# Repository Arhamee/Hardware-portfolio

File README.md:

<div align="center">

# ⚡ Hardware Portfolio
### Arham Amir

**Electronics Engineering @ NED University, Karachi** · Class of 2028

Multi-layer PCB designs — schematic capture to fabrication-ready output.  
Every board includes the full KiCad source, renders, and DRC verification.

</div>

---

## 📂 Projects

| # | Project | Layers | Key Focus | Status |
|:---:|---|:---:|---|:---:|
| 01 | **[LattePanda Mu Carrier Board](./01-LattePanda-Mu-Carrier-Board)** | 4 | USB 3.0 · HDMI · GbE, controlled impedance | 🟡 In Progress |
| 02 | **[BGA Smart USB Drive](./02-BGA-Smart-USB-Drive)** | 4 | RP2040 + 64GB eMMC, 0.5mm BGA escape | 🟢 Complete |
| 03 | **[Industrial APFC System](./03-Industrial-APFC-System)** | 4 | 5kW single-phase, mains isolation | 🟢 Complete |
| 04 | **[STM32WB USB + RF Board](./04-STM32WB-USB-RF)** | 4 | 2.4GHz RF + USB, dual-ground stackup | 🟢 Complete |
| 05 | **[USB-C PD Power Supply](./05-USBC-PD-Power-Supply)** | 2 | CH224K PD negotiation, 90Ω diff pairs | 🟢 Complete |
| 06 | **[ESP32 Power Monitor](./06-ESP32-Power-Monitor)** | 4 | 5-channel relay + current sensing | 🟢 Complete |
| 07 | **[Hearing Assist DSP](./07-Hearing-Assist-DSP)** | — | Real-time NLMS noise cancellation | ✅ Built & Tested |
| 09 | **[MCU Board Collection](./09-MCU-Board-Collection)** | 2–4 | ESP32 / STM32 / MSPM0 variants | 🟢 Mixed |

---

## 🛠️ Technical Focus

<table>
<tr>
<td valign="top" width="50%">

**PCB Design**
- Controlled-impedance routing
- Differential pair matching
- Fine-pitch BGA fanout (via-in-pad, dogbone)
- Multi-layer stackup planning
- PDN design across multiple rails
- DFM / DRC verification

</td>
<td valign="top" width="50%">

**Embedded & Digital**
- ESP32 · STM32 · RP2040 · TI MSPM0
- FreeRTOS · real-time DSP
- Verilog RTL · FSM design
- ModelSim simulation

</td>
</tr>
<tr>
<td valign="top" colspan="2">

**Power Electronics**
- Mains-side isolation
- Protection: MOV, TVS, fusing
- SSR switching · boost/LDO regulation

</td>
</tr>
</table>
---
## 📁 Repository Structure

Each project folder follows the same layout:

```
project-name/
├── README.md              — design overview, challenges, decisions
├── kicad-project/          — full KiCad source (.kicad_pro/.sch/.pcb)
├── schematic.pdf           — exported schematic view
├── pcb-layout-top.png      — routed board, top view
├── 3d-render-top.png       — 3D render
├── drc-report.png          — DRC/ERC verification result
└── gerbers.zip             — fabrication-ready Gerbers + drill files
```

> Every board ships with its **raw KiCad files** — not just images — so the
> design can be opened, checked, and verified directly rather than taken on faith.
### 🔍 Fabrication Status

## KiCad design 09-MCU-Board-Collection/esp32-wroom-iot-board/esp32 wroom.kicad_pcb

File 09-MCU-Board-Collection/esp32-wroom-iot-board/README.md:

# General-Purpose IoT Board — ESP32-WROOM

4-layer board built around the ESP32-WROOM module as a versatile, expandable
IoT development platform.

## Features
- **Si7021** — I²C temperature and humidity sensor
- **QWIIC connector** — plug-and-play expansion for other I²C devices
- **CP2104** — USB-to-serial UART with onboard programmer, no external
  programmer needed
- **RGB LED + button** — status indication and user input
- **Screw terminals** — LED strip interface, 4-level converted outputs,
  fused power supply
- **Power relay** — control for high-power devices (lights, motors, appliances)

## Why 4 layers
Cleaner routing and better signal integrity for the ESP32's high-speed
requirements, especially with multiple peripherals sharing the board.

## Tool
KiCad 9

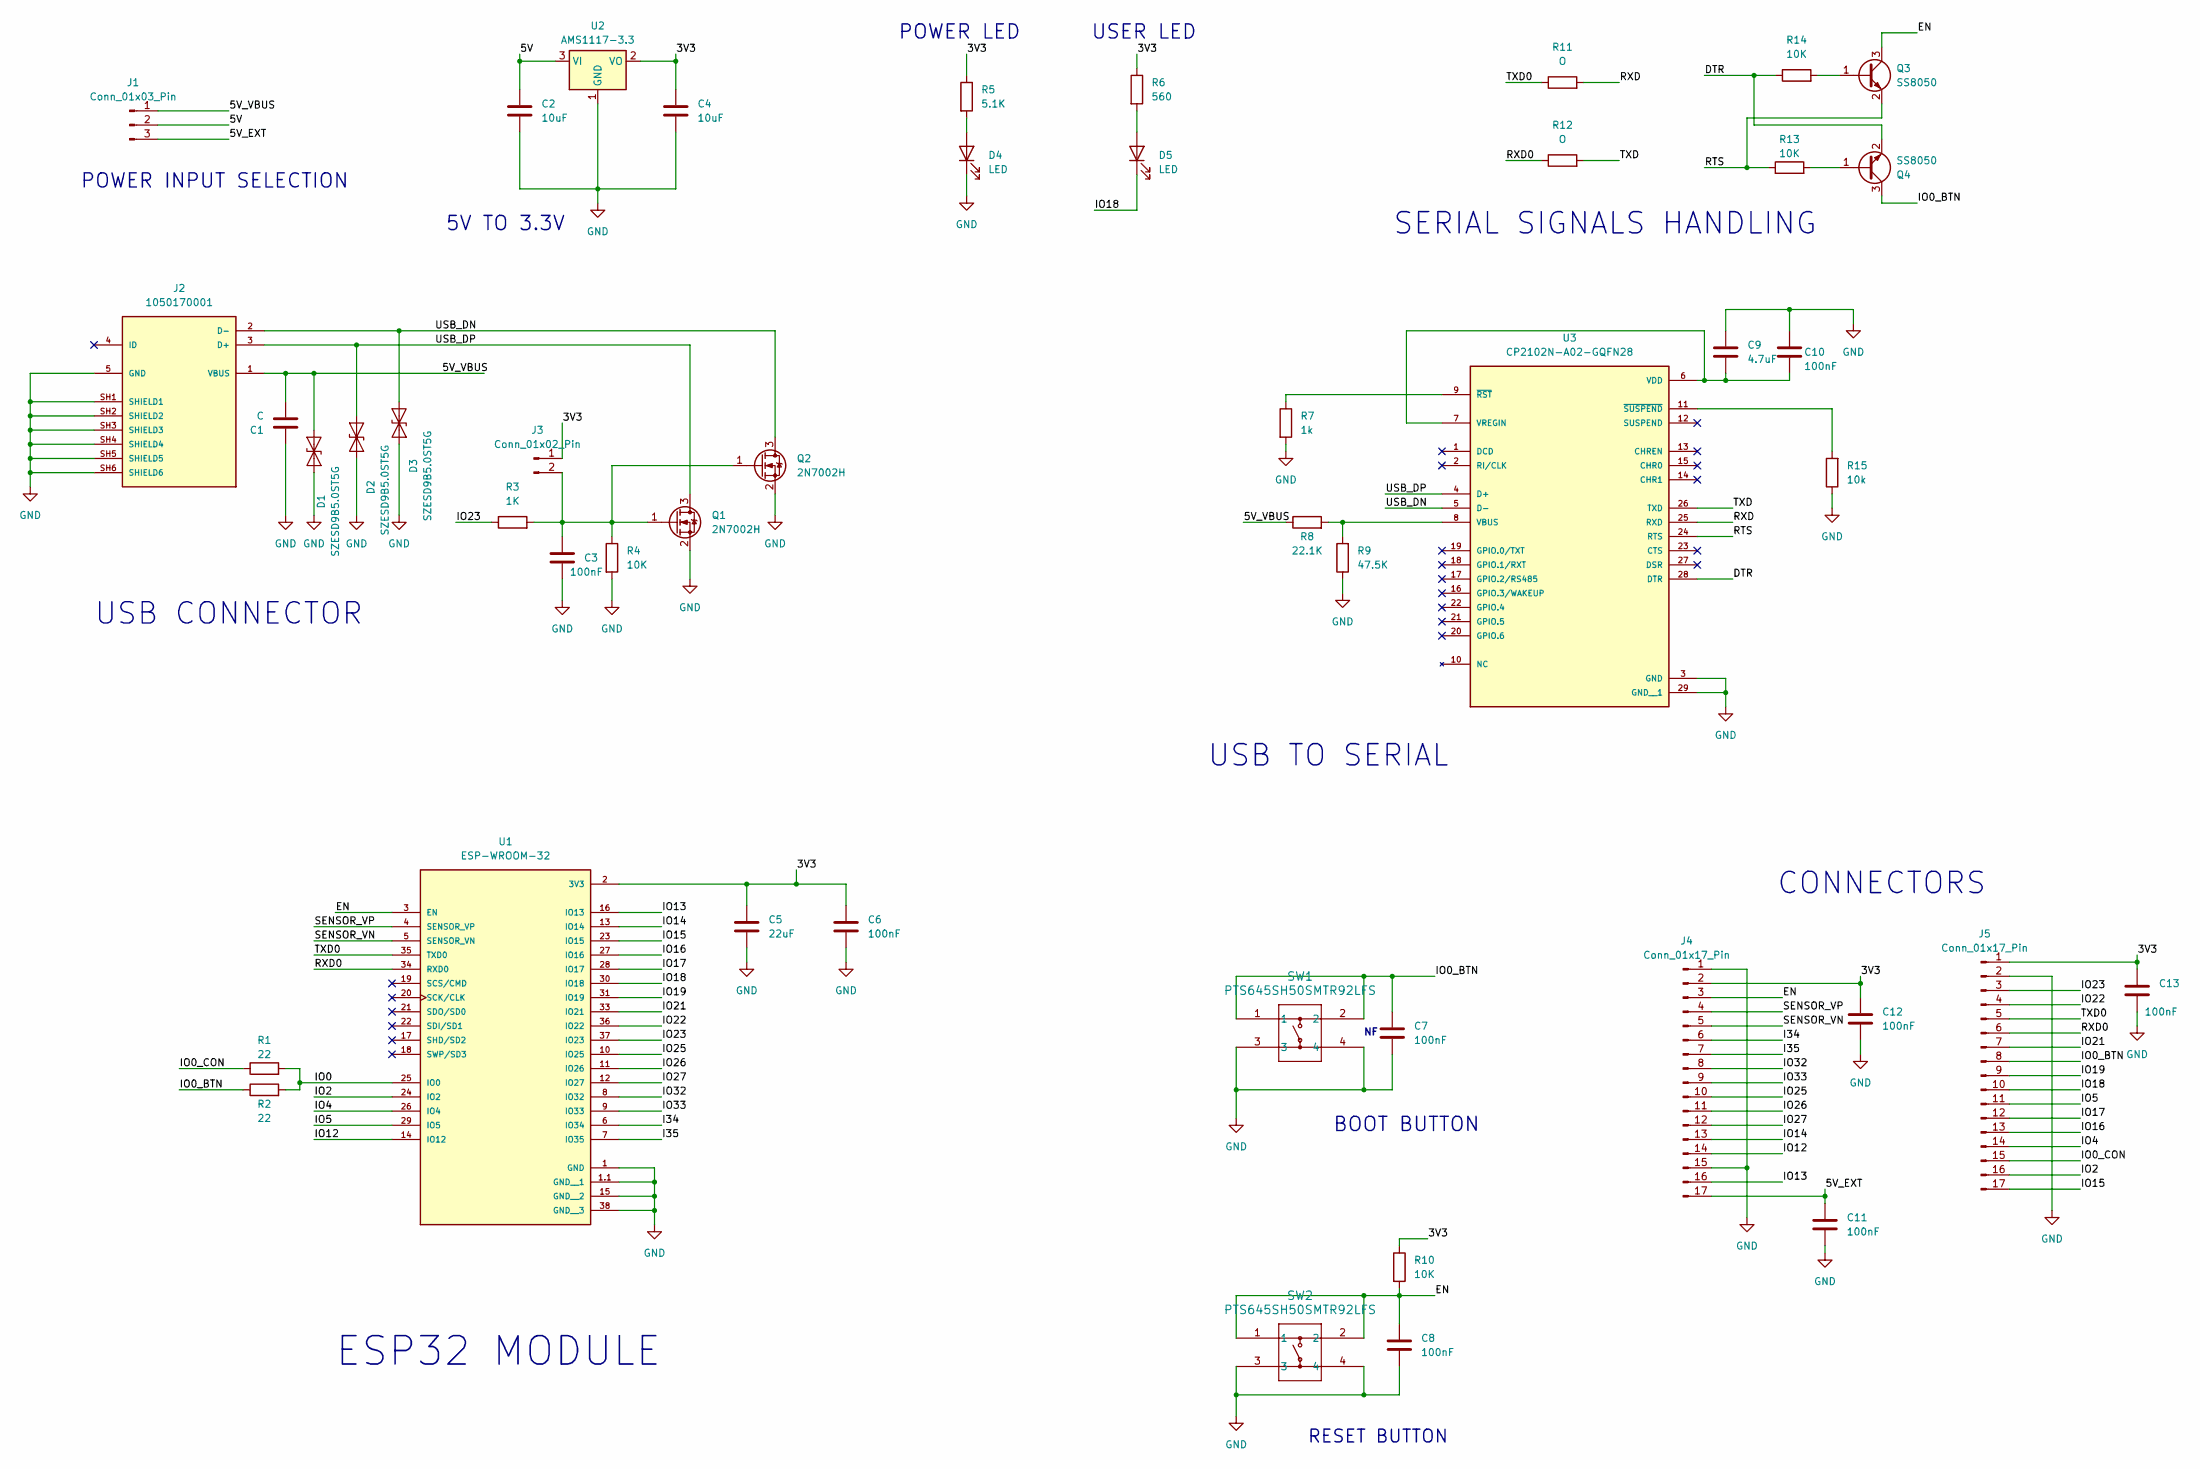
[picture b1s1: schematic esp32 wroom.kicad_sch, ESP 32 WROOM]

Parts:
C1: C; C_0402_1005Metric_Pad0.74x0.62mm_HandSolder
C2, C4: 10uF; C_0402_1005Metric_Pad0.74x0.62mm_HandSolder
C3, C6, C7, C8, C10, C11, C12, C13: 100nF; C_0402_1005Metric_Pad0.74x0.62mm_HandSolder
C5: 22uF; C_0402_1005Metric_Pad0.74x0.62mm_HandSolder
C9: 4.7uF; C_0402_1005Metric_Pad0.74x0.62mm_HandSolder
D1, D2, D3: SZESD9B5.0ST5G; D_SOD-923
D4, D5: LED; LED_0402_1005Metric_Pad0.77x0.64mm_HandSolder
J1: Conn_01x03_Pin; PinHeader_1x03_P1.27mm_Vertical
J2: 1050170001; MOLEX_1050170001; PARTREV F
J3: Conn_01x02_Pin; PinHeader_1x02_P1.27mm_Vertical
J4, J5: Conn_01x17_Pin; PinHeader_1x17_P1.27mm_Vertical
Q1, Q2: 2N7002H; SOT-23
Q3, Q4: SS8050; SOT-23
R1, R2: 22; R_0402_1005Metric_Pad0.72x0.64mm_HandSolder
R3: 1K; R_0402_1005Metric_Pad0.72x0.64mm_HandSolder
R4, R10, R13, R14: 10K; R_0402_1005Metric_Pad0.72x0.64mm_HandSolder
R5: 5.1K; R_0402_1005Metric_Pad0.72x0.64mm_HandSolder
R6: 560; R_0402_1005Metric_Pad0.72x0.64mm_HandSolder
R7: 1k; R_0402_1005Metric_Pad0.72x0.64mm_HandSolder
R8: 22.1K; R_0402_1005Metric_Pad0.72x0.64mm_HandSolder
R9: 47.5K; R_0402_1005Metric_Pad0.72x0.64mm_HandSolder
R11, R12: O; R_0402_1005Metric_Pad0.72x0.64mm_HandSolder
R15: 10k; R_0402_1005Metric_Pad0.72x0.64mm_HandSolder
SW1, SW2: PTS645SH50SMTR92LFS; PTS645S_SMTR92_CNK
U1: ESP-WROOM-32; MODULE_ESP-WROOM-32
U2: AMS1117-3.3; SOT-223-3_TabPin2
U3: CP2102N-A02-GQFN28; QFN50P500X500X80-29N; PARTREV 1.5

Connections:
/3V3: C4.1, C5.1, C6.1, C12.1, C13.1, J3.1, J4.2, J5.1, R5.1, R6.1, R10.1, U1.2 (3V3), U2.2 (VO)
/5V: C2.1, J1.2, U2.3 (VI)
/5V_EXT: C11.1, J1.3, J4.17
/5V_VBUS: C1.2, D1.2 (A2), J1.1, J2.1 (VBUS), R8.1
/DTR: Q4.2 (E), R14.1, U3.28 (DTR)
/EN: C8.1, J4.3, Q3.3 (C), R10.2, SW2.1, SW2.2, U1.3 (EN)
/I34: J4.6, U1.6 (IO34)
/I35: J4.7, U1.7 (IO35)
/IO0: R1.2, R2.2, U1.25 (IO0)
/IO0_BTN: C7.1, J5.8, Q4.3 (C), R2.1, SW1.1, SW1.2
/IO0_CON: J5.15, R1.1
/IO2: J5.16, U1.24 (IO2)
/IO4: J5.14, U1.26 (IO4)
/IO5: J5.11, U1.29 (IO5)
/IO12: J4.14, U1.14 (IO12)
/IO13: J4.16, U1.16 (IO13)
/IO14: J4.13, U1.13 (IO14)
/IO15: J5.17, U1.23 (IO15)
/IO16: J5.13, U1.27 (IO16)
/IO17: J5.12, U1.28 (IO17)
/IO18: D5.1 (K), J5.10, U1.30 (IO18)
/IO19: J5.9, U1.31 (IO19)
/IO21: J5.7, U1.33 (IO21)
/IO22: J5.4, U1.36 (IO22)
/IO23: J5.3, R3.1, U1.37 (IO23)
/IO25: J4.10, U1.10 (IO25)
/IO26: J4.11, U1.11 (IO26)
/IO27: J4.12, U1.12 (IO27)
/IO32: J4.8, U1.8 (IO32)
/IO33: J4.9, U1.9 (IO33)
/RTS: Q3.2 (E), R13.1, U3.24 (RTS)
/RXD: R11.2, U3.25 (RXD)
/RXD0: J5.6, R12.1, U1.34 (RXD0)
/SENSOR_VN: J4.5, U1.5 (SENSOR_VN)
/SENSOR_VP: J4.4, U1.4 (SENSOR_VP)
/TXD: R12.2, U3.26 (TXD)
/TXD0: J5.5, R11.1, U1.35 (TXD0)
/USB_DN: D3.2 (A2), J2.2 (D-), Q2.3 (D), U3.5 (D-)
/USB_DP: D2.2 (A2), J2.3 (D+), Q1.3 (D), U3.4 (D+)
GND: C1.1, C2.2, C3.2, C4.2, C5.2, C6.2, C7.2, C8.2, C9.1, C10.1, C11.2, C12.2, C13.2, D1.1 (A1), D2.1 (A1), D3.1 (A1), D4.1 (K), J2.5 (GND), J2.SH1 (SHIELD1), J2.SH2 (SHIELD2), J2.SH3 (SHIELD3), J2.SH4 (SHIELD4), J2.SH5 (SHIELD5), J2.SH6 (SHIELD6), J4.1, J4.15, J5.2, Q1.2 (S), Q2.2 (S), R4.2, R7.2, R9.1, R15.1, SW1.3, SW1.4, SW2.3, SW2.4, U1.1 (GND), U1.1.1 (GND__1), U1.15 (GND__2), U1.38 (GND__3), U2.1 (GND), U3.3 (GND), U3.29 (GND__1)
unnamed: D4.2 (A), R5.2
unnamed: D5.2 (A), R6.2
unnamed: C3.1, J3.2, Q1.1 (G), Q2.1 (G), R3.2, R4.1
unnamed: Q3.1 (B), R14.2
unnamed: Q4.1 (B), R13.2
unnamed: R8.2, R9.2, U3.8 (VBUS)
unnamed: C9.2, C10.2, U3.6 (VDD), U3.7 (VREGIN)
unnamed: R7.1, U3.9 (~RST)
unnamed: R15.2, U3.11 (~SUSPEND)

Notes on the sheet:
USB TO SERIAL
SERIAL SIGNALS HANDLING
ESP32 MODULE
USB CONNECTOR
BOOT BUTTON
USER LED
RESET BUTTON
POWER INPUT SELECTION
POWER LED
CONNECTORS
5V TO 3.3V

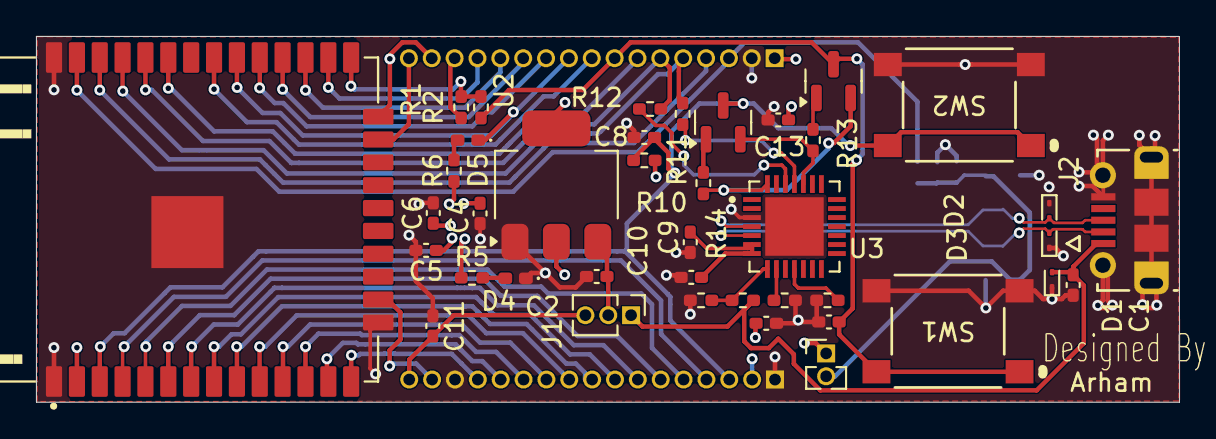
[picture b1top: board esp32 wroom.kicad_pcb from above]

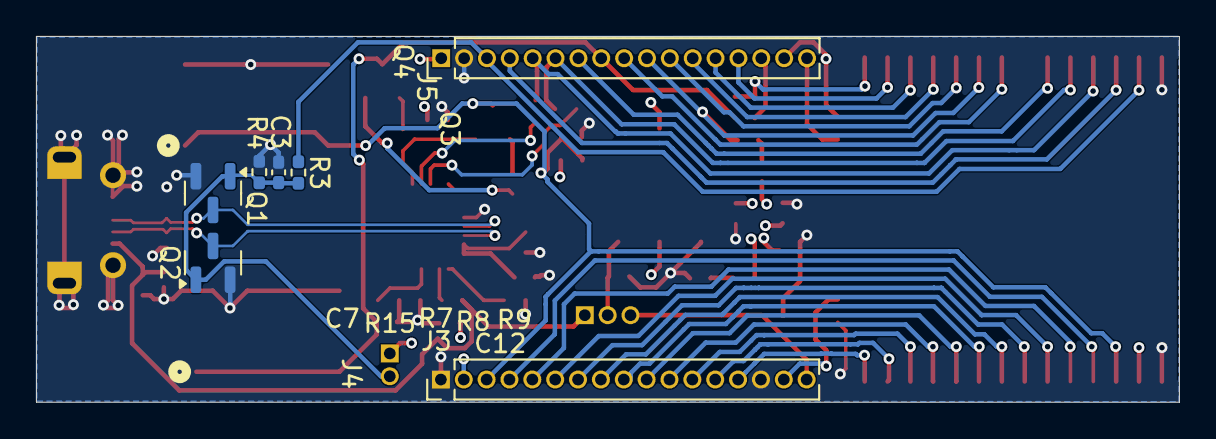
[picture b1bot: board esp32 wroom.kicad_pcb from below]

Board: 4 copper layers, 63.5 x 20.3 mm, 47 parts (7 on the bottom side), 49 nets.

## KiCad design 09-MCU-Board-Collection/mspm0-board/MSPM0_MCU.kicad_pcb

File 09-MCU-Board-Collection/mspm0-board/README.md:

# MSPM0 Board — TI ARM Cortex-M0+

First design using Texas Instruments' MSPM0 family.

## Focus Areas
- Clean power delivery
- Robust USB connectivity
- MCU-to-peripheral signal routing
- Careful attention to datasheet guidance for decoupling, crystal layout,
  and USB differential pairs

## Tool
KiCad 9

## Reference
Built following Phil's Lab's MSPM0 hardware tutorial.

## Status
Design complete — assembly and testing planned.

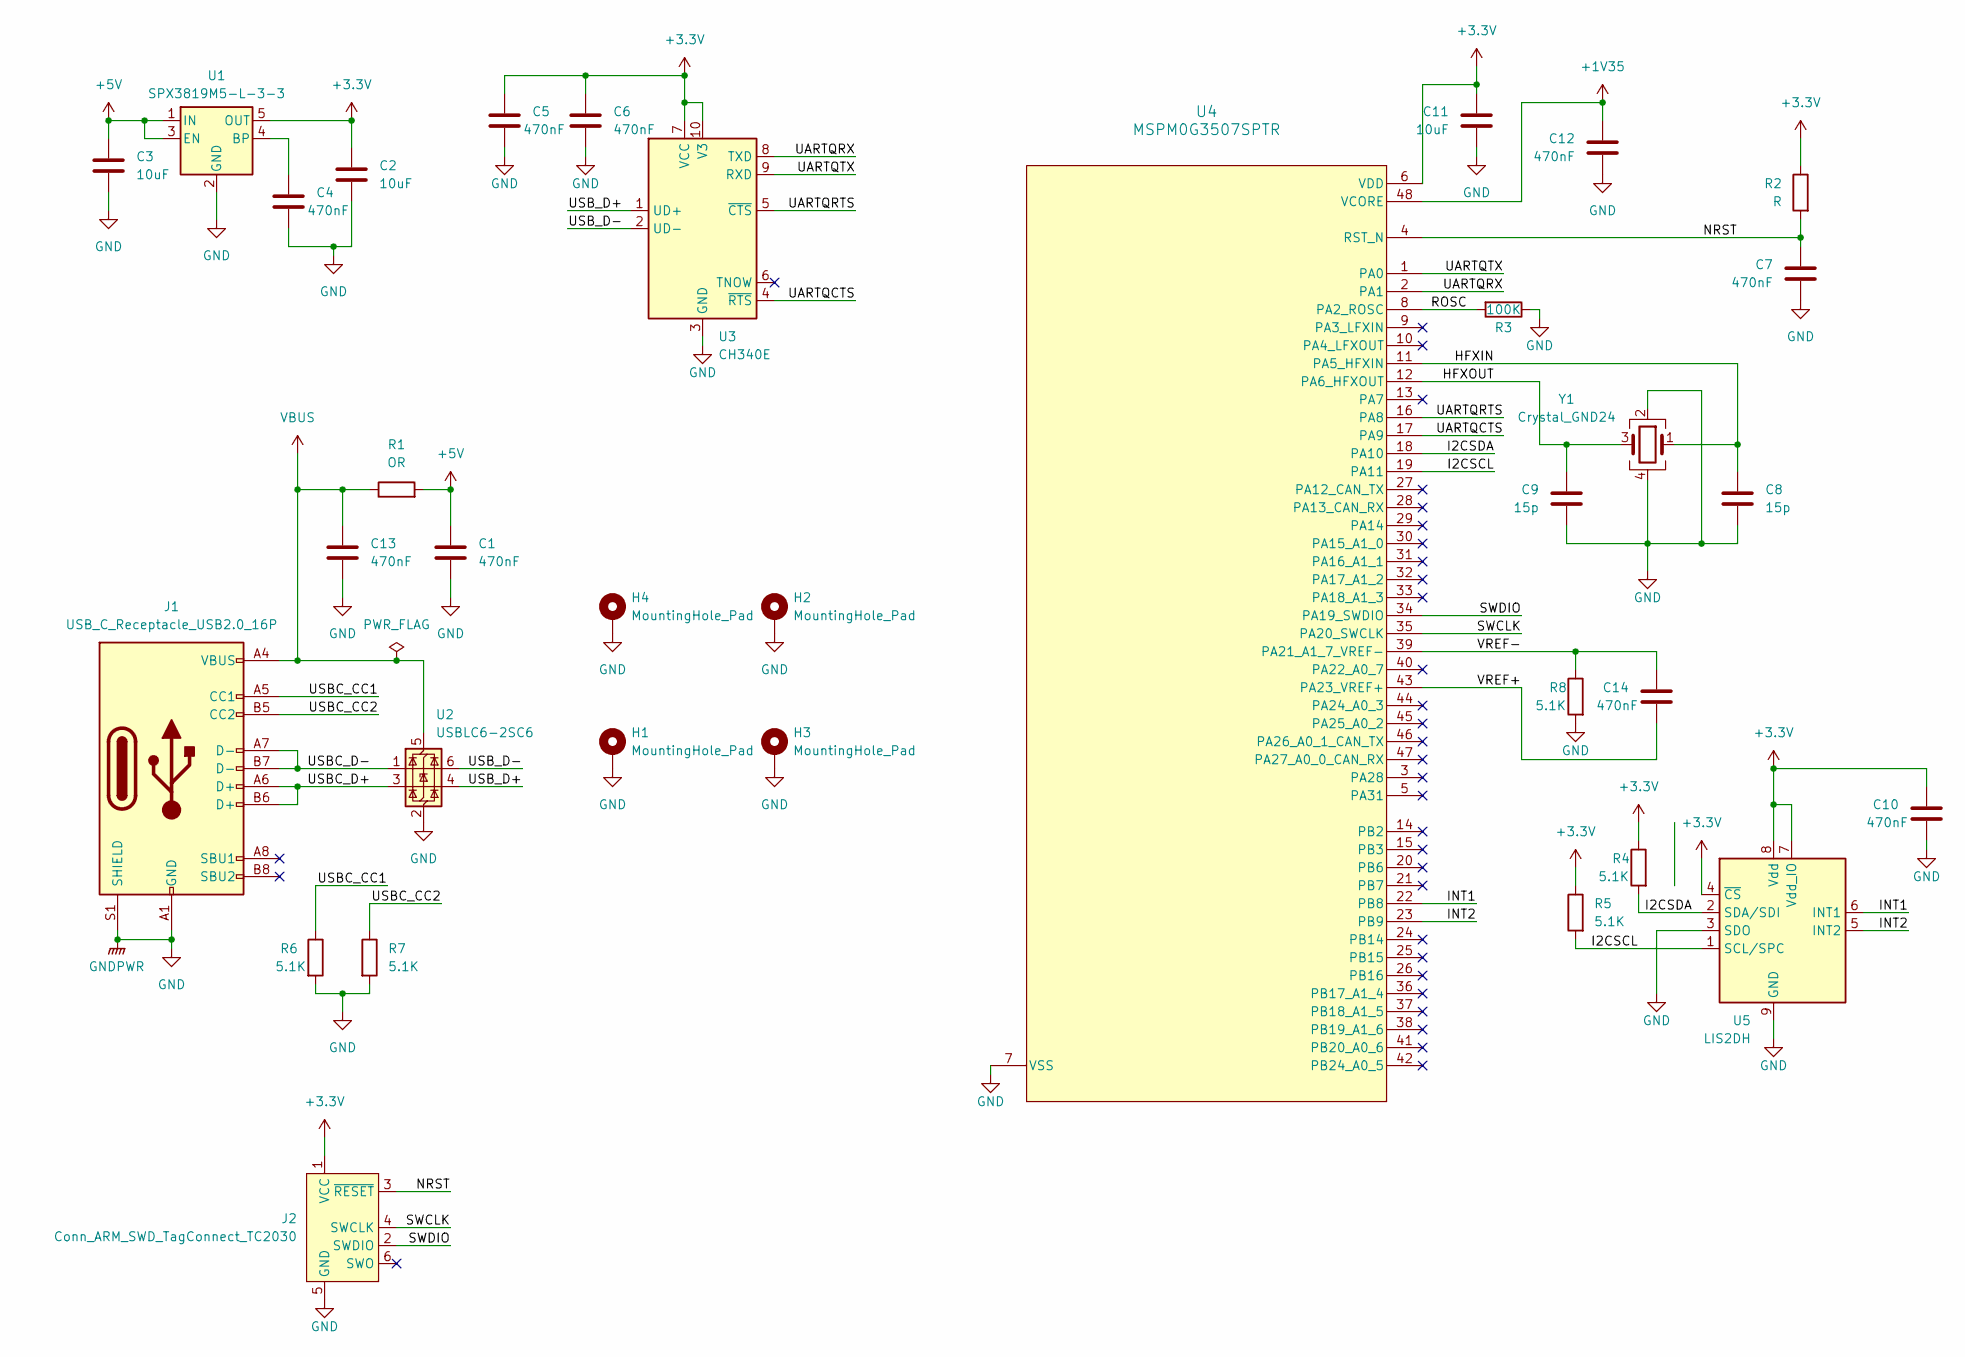
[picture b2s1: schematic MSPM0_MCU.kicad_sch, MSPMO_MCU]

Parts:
C1, C4, C5, C6, C7, C10, C12, C13, C14: 470nF; C_0603_1608Metric_Pad1.08x0.95mm_HandSolder
C2, C3, C11: 10uF; C_0805_2012Metric_Pad1.18x1.45mm_HandSolder
C8, C9: 15p; C_0603_1608Metric_Pad1.08x0.95mm_HandSolder
H1, H2, H3, H4: MountingHole_Pad; MountingHole_3.2mm_M3_Pad_Via
J1: USB_C_Receptacle_USB2.0_16P; USB_C_Receptacle_GCT_USB4105-xx-A_16P_TopMnt_Horizontal
J2: Conn_ARM_SWD_TagConnect_TC2030; Tag-Connect_TC2030-IDC-FP_2x03_P1.27mm_Vertical
R1: OR; R_0603_1608Metric_Pad0.98x0.95mm_HandSolder
R2: R; R_0603_1608Metric_Pad0.98x0.95mm_HandSolder
R3: 100K; R_0603_1608Metric_Pad0.98x0.95mm_HandSolder
R4, R5, R6, R7, R8: 5.1K; R_0603_1608Metric_Pad0.98x0.95mm_HandSolder
U1: SPX3819M5-L-3-3; SOT-23-5
U2: USBLC6-2SC6; SOT-23-6
U3: CH340E; MSOP-10_3x3mm_P0.5mm
U4: MSPM0G3507SPTR; PT0048A-IPC_A
U5: LIS2DH; LGA-14_2x2mm_P0.35mm_LayoutBorder3x4y
Y1: Crystal_GND24; Crystal_SMD_3225-4Pin_3.2x2.5mm_HandSoldering

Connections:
+1V35: C12.1, U4.48 (VCORE)
+3.3V: C2.1, C5.1, C6.1, C10.1, C11.1, J2.1 (VCC), R2.1, R4.1, R5.1, U1.5 (OUT), U3.7 (VCC), U3.10 (V3), U4.6 (VDD), U5.4 (~CS), U5.7 (Vdd_IO), U5.8 (Vdd)
+5V: C1.1, C3.1, R1.2, U1.1 (IN), U1.3 (EN)
/HFXIN: C8.1, U4.11 (PA5_HFXIN), Y1.1
/HFXOUT: C9.1, U4.12 (PA6_HFXOUT), Y1.3
/I2CSCL: R5.2, U4.19 (PA11), U5.1 (SCL/SPC)
/I2CSDA: R4.2, U4.18 (PA10), U5.2 (SDA/SDI)
/INT1: U4.22 (PB8), U5.6 (INT1)
/INT2: U4.23 (PB9), U5.5 (INT2)
/NRST: C7.1, J2.3 (~RESET), R2.2, U4.4 (RST_N)
/ROSC: R3.2, U4.8 (PA2_ROSC)
/SWCLK: J2.4 (SWCLK), U4.35 (PA20_SWCLK)
/SWDIO: J2.2 (SWDIO), U4.34 (PA19_SWDIO)
/UARTQCTS: U3.4 (~RTS), U4.17 (PA9)
/UARTQRTS: U3.5 (~CTS), U4.16 (PA8)
/UARTQRX: U3.8 (TXD), U4.2 (PA1)
/UARTQTX: U3.9 (RXD), U4.1 (PA0)
/USBC_CC1: J1.A5 (CC1), R6.1
/USBC_CC2: J1.B5 (CC2), R7.1
/USBC_D+: J1.A6 (D+), J1.B6 (D+), U2.3 (I/O2)
/USBC_D-: J1.A7 (D-), J1.B7 (D-), U2.1 (I/O1)
/USB_D+: U2.4 (I/O2), U3.1 (UD+)
/USB_D-: U2.6 (I/O1), U3.2 (UD-)
/VREF+: C14.2, U4.43 (PA23_VREF+)
/VREF-: C14.1, R8.1, U4.39 (PA21_A1_7_VREF-)
GND: C1.2, C2.2, C3.2, C4.2, C5.2, C6.2, C7.2, C8.2, C9.2, C10.2, C11.2, C12.2, C13.2, H1.1, H2.1, H3.1, H4.1, J1.A1 (GND), J1.A12 (GND), J1.B1 (GND), J1.B12 (GND), J1.S1 (SHIELD), J2.5 (GND), R3.1, R6.2, R7.2, R8.2, U1.2 (GND), U2.2 (GND), U3.3 (GND), U4.7 (VSS), U5.3 (SDO), U5.9 (GND), U5.10 (GND), U5.11 (GND), U5.12 (GND), U5.13 (GND), U5.14 (GND), Y1.2, Y1.4
unnamed: C4.1, U1.4 (BP)
VBUS: C13.1, J1.A4 (VBUS), J1.A9 (VBUS), J1.B4 (VBUS), J1.B9 (VBUS), R1.1, U2.5 (VBUS)

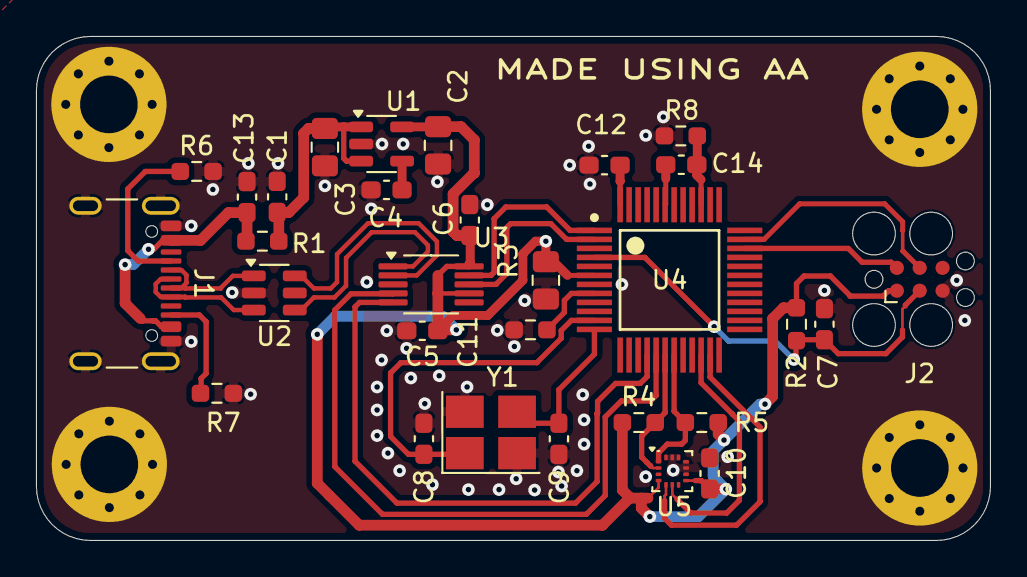
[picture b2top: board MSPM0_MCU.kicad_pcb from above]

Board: 2 copper layers, 53.0 x 28.0 mm, 34 parts (0 on the bottom side), 28 nets.

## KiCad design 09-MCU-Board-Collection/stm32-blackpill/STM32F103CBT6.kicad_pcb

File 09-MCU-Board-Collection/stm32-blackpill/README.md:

# STM32 "Black Pill" Board

First full PCB design completed end-to-end in KiCad 9 — schematic through
2-layer layout and routing.

## Included
- Power management (3.3V LDO)
- Reset circuitry and BOOT configuration
- USB Type-B Micro with proper D+/D− routing
- Careful component placement for signal integrity on a 2-layer board
- DRC passed — ready for prototype manufacturing

## What This Taught Me
MCU power requirements, decoupling strategy, and high-speed signal
considerations — even on a "simple" 2-layer board.

## Reference
Built following Phil Salmony's (Phil's Lab) PCB Design Course.

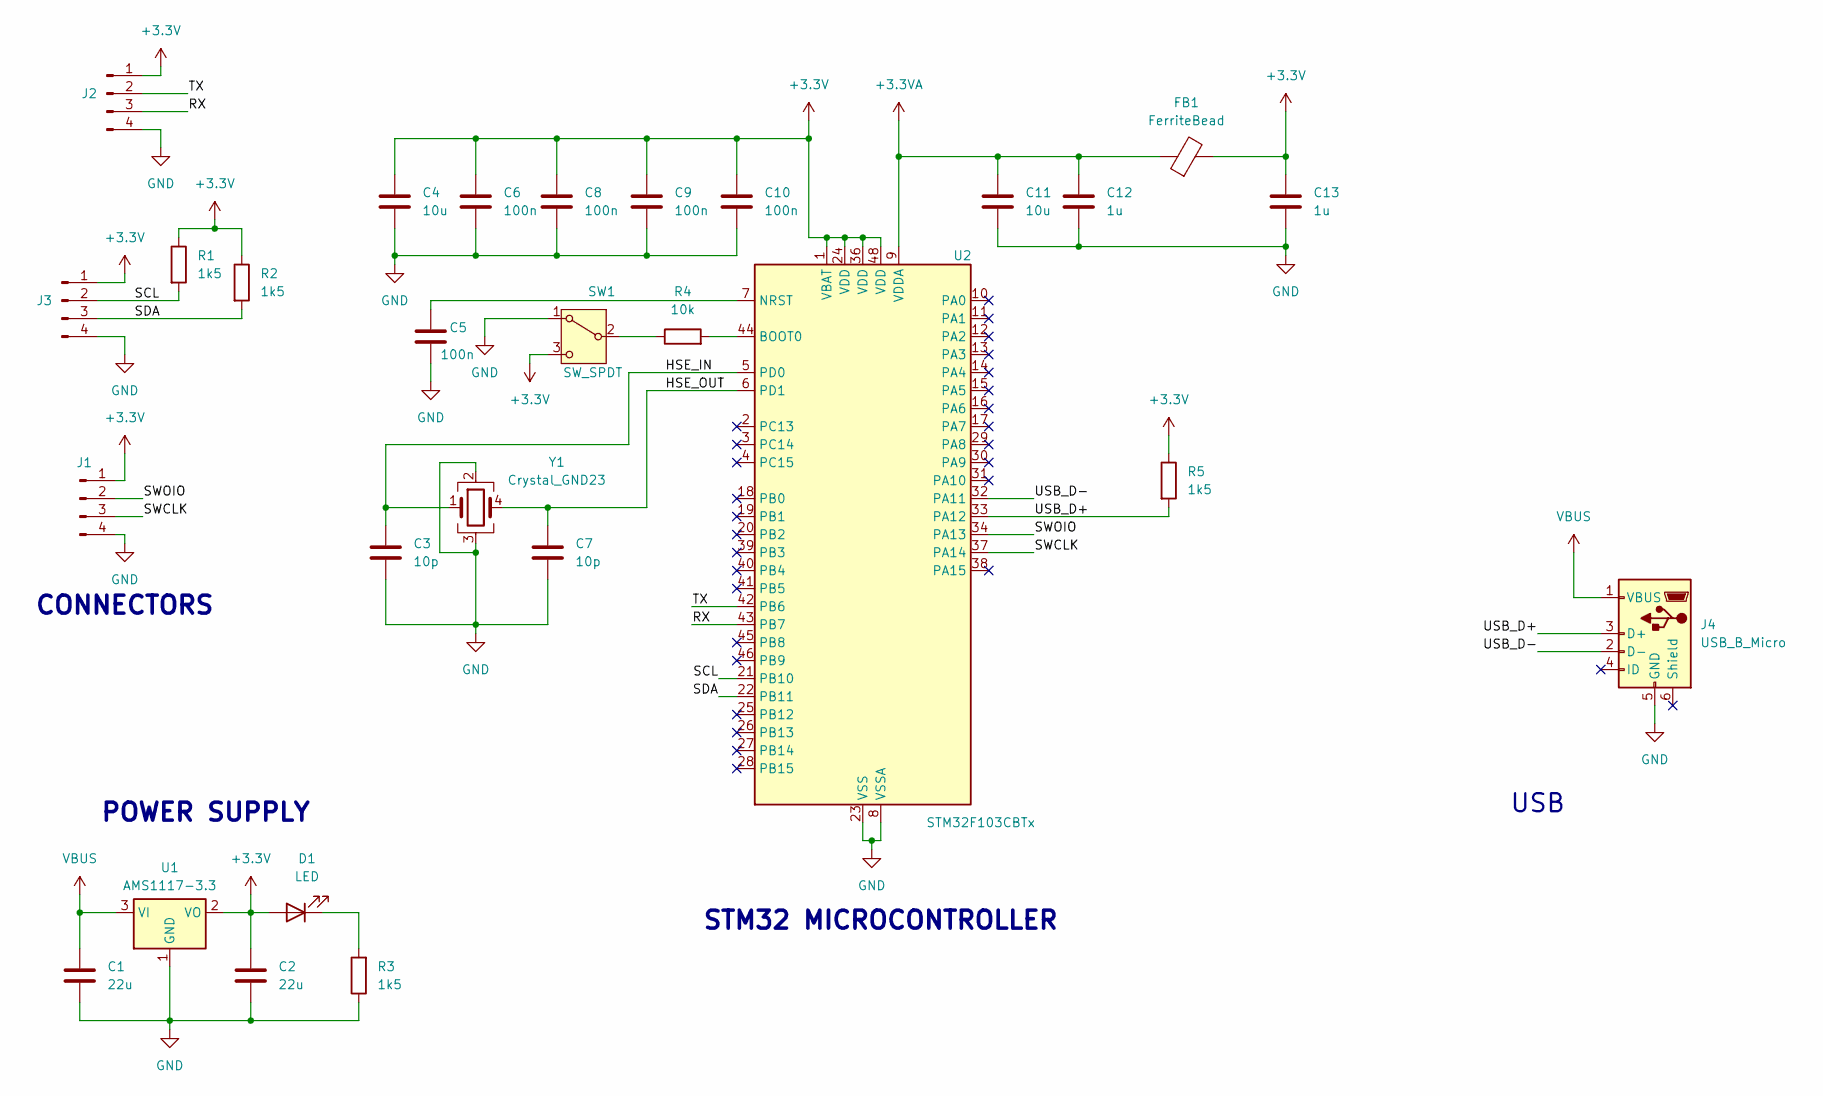
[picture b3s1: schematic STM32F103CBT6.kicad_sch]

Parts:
C1, C2: 22u; C_0805_2012Metric_Pad1.18x1.45mm_HandSolder
C3, C7: 10p; C_0402_1005Metric_Pad0.74x0.62mm_HandSolder
C4: 10u; C_0402_1005Metric_Pad0.74x0.62mm_HandSolder
C5, C6, C8, C9, C10: 100n; C_0402_1005Metric_Pad0.74x0.62mm_HandSolder
C11: 10u; C_0603_1608Metric_Pad1.08x0.95mm_HandSolder
C12, C13: 1u; C_0402_1005Metric_Pad0.74x0.62mm_HandSolder
D1: LED; LED_0201_0603Metric_Pad0.64x0.40mm_HandSolder
FB1: FerriteBead; L_0201_0603Metric_Pad0.64x0.40mm_HandSolder
J1, J2, J3: Conn_01x04_Pin; PinHeader_1x04_P2.54mm_Vertical
J4: USB_B_Micro; USB_Micro-B_Wuerth_629105150521
R1, R2, R3, R5: 1k5; R_0402_1005Metric_Pad0.72x0.64mm_HandSolder
R4: 10k; R_0402_1005Metric_Pad0.72x0.64mm_HandSolder
SW1: SW_SPDT; SW_Slide-03_Wuerth-WS-SLTV_10x2.5x6.4_P2.54mm
U1: AMS1117-3.3; SOT-223-3_TabPin2
U2: STM32F103CBTx; LQFP-48_7x7mm_P0.5mm
Y1: Crystal_GND23; Crystal_SMD_3225-4Pin_3.2x2.5mm

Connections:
+3.3V: C2.1, C4.1, C6.1, C8.1, C9.1, C10.1, C13.1, D1.2 (A), FB1.2, J1.1, J2.1, J3.1, R1.1, R2.1, R5.1, SW1.3 (C), U1.2 (VO), U2.1 (VBAT), U2.24 (VDD), U2.36 (VDD), U2.48 (VDD)
+3.3VA: C11.1, C12.1, FB1.1, U2.9 (VDDA)
/HSE_IN: C3.1, U2.5 (PD0), Y1.1
/HSE_OUT: C7.1, U2.6 (PD1), Y1.4
/RX: J2.3, U2.43 (PB7)
/SCL: J3.2, R1.2, U2.21 (PB10)
/SDA: J3.3, R2.2, U2.22 (PB11)
/SWCLK: J1.3, U2.37 (PA14)
/SWOIO: J1.2, U2.34 (PA13)
/TX: J2.2, U2.42 (PB6)
/USB_D+: J4.3 (D+), R5.2, U2.33 (PA12)
/USB_D-: J4.2 (D-), U2.32 (PA11)
GND: C1.2, C2.2, C3.2, C4.2, C5.2, C6.2, C7.2, C8.2, C9.2, C10.2, C11.2, C12.2, C13.2, J1.4, J2.4, J3.4, J4.5 (GND), R3.1, SW1.1 (A), U1.1 (GND), U2.8 (VSSA), U2.23 (VSS), U2.35 (VSS), U2.47 (VSS), Y1.2, Y1.3
unnamed: D1.1 (K), R3.2
unnamed: R4.1, SW1.2 (B)
unnamed: R4.2, U2.44 (BOOT0)
unnamed: C5.1, U2.7 (NRST)
VBUS: C1.1, J4.1 (VBUS), U1.3 (VI)

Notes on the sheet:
POWER SUPPLY
STM32 MICROCONTROLLER
CONNECTORS
USB

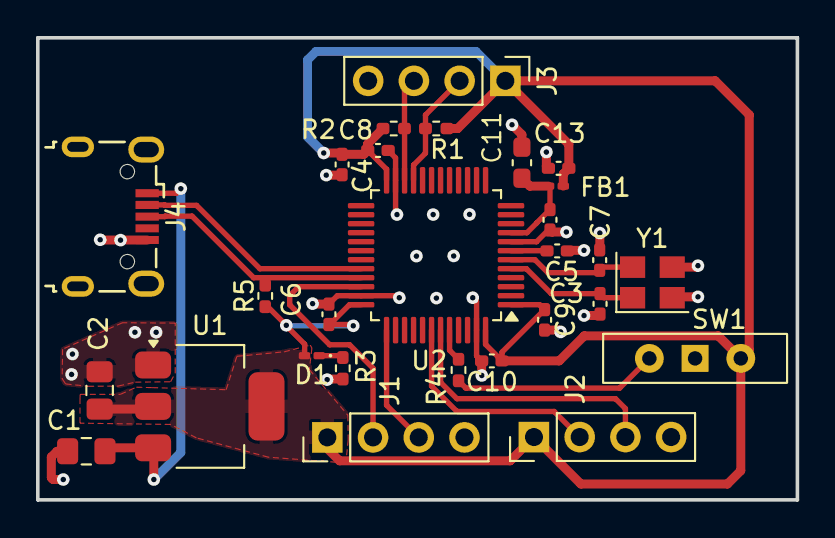
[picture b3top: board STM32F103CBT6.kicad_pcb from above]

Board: 2 copper layers, 42.2 x 25.7 mm, 28 parts (0 on the bottom side), 18 nets.

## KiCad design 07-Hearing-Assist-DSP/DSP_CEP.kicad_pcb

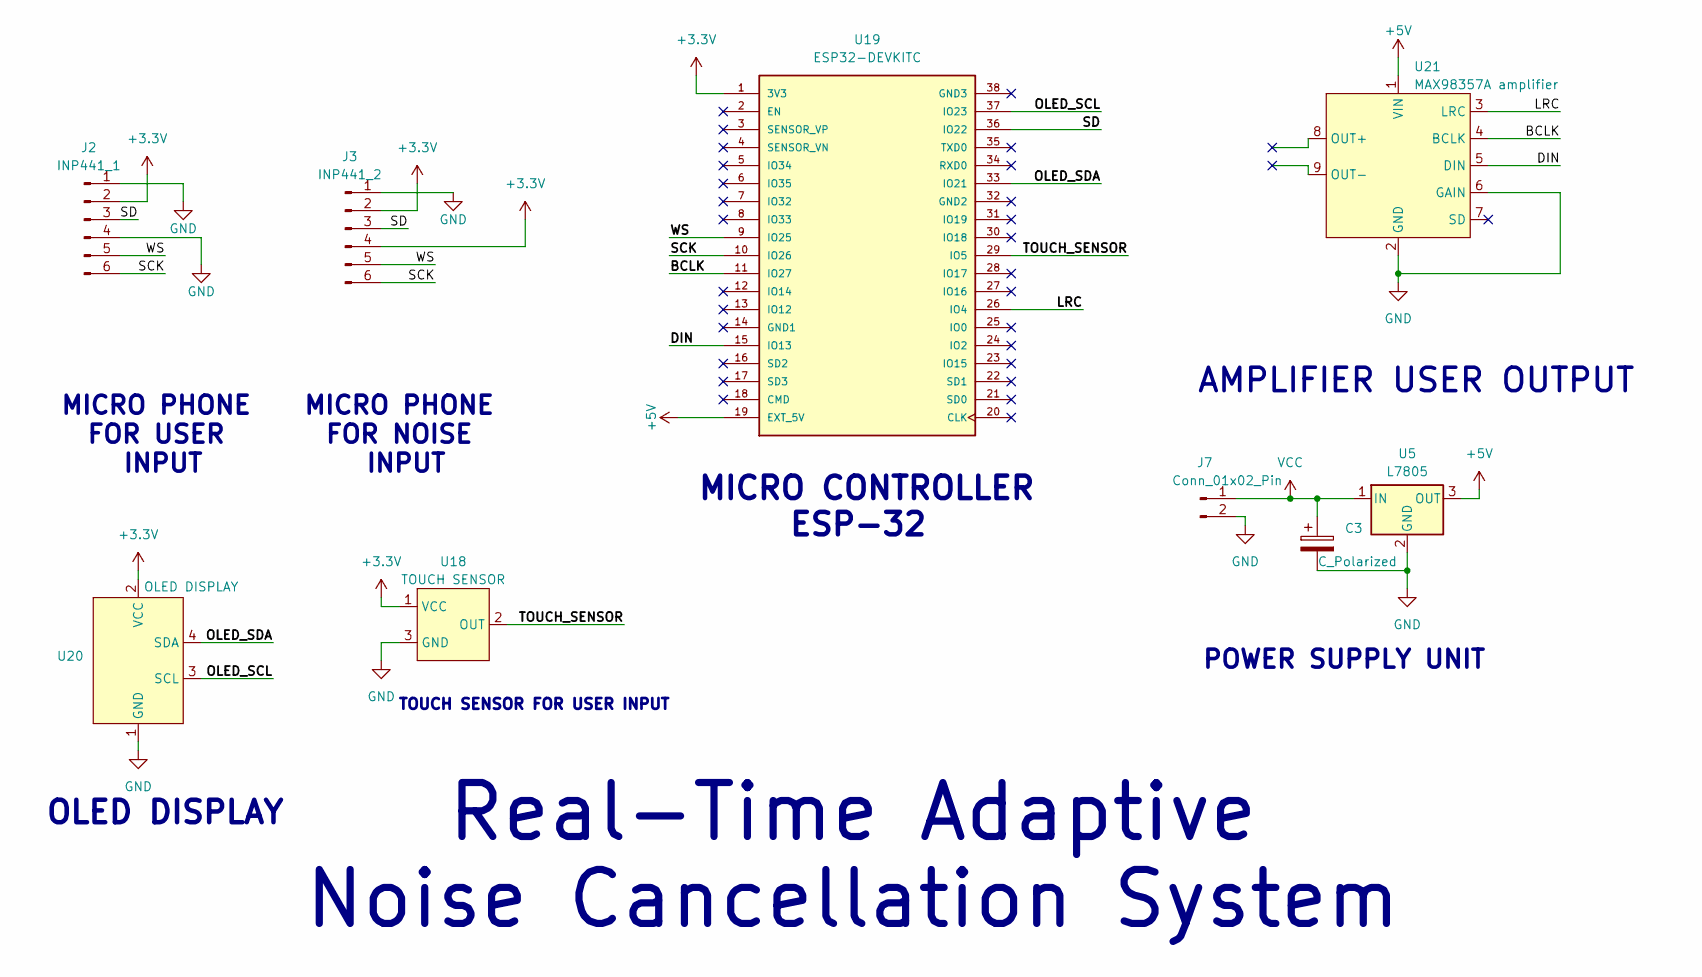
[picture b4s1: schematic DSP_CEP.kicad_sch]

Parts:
C3: C_Polarized; CP_Radial_D10.0mm_P5.00mm
J2: INP441_1; PinHeader_1x06_P2.54mm_Vertical
J3: INP441_2; PinHeader_1x06_P2.54mm_Vertical
J7: Conn_01x02_Pin; PinHeader_1x02_P2.54mm_Vertical
U5: L7805; TO-220-3_Vertical
U18: TOUCH SENSOR; PinHeader_1x03_P2.54mm_Vertical
U19: ESP32-DEVKITC; MODULE_DEVKIT_V1_ESP32-WROOM-32; PARTREV N/A
U20: OLED DISPLAY; PinHeader_1x04_P2.54mm_Vertical
U21: MAX98357A amplifier; PinHeader_1x07_P2.54mm_Vertical

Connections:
+3.3V: J2.2, J3.2, J3.4, U18.1 (VCC), U19.1 (3V3), U20.2 (VCC)
+5V: U5.3 (OUT), U19.19 (EXT_5V), U21.1 (VIN)
/BCLK: U19.11 (IO27), U21.4 (BCLK)
/DIN: U19.15 (IO13), U21.5 (DIN)
/LRC: U19.26 (IO4), U21.3 (LRC)
/OLED_SCL: U19.37 (IO23), U20.3 (SCL)
/OLED_SDA: U19.33 (IO21), U20.4 (SDA)
/SCK: J2.6, J3.6, U19.10 (IO26)
/SD: J2.3, J3.3, U19.36 (IO22)
/TOUCH_SENSOR: U18.2 (OUT), U19.29 (IO5)
/WS: J2.5, J3.5, U19.9 (IO25)
GND: C3.2, J2.1, J2.4, J3.1, J7.2, U5.2 (GND), U18.3 (GND), U20.1 (GND), U21.2 (GND), U21.6 (GAIN)
VCC: C3.1, J7.1, U5.1 (IN)

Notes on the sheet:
AMPLIFIER USER OUTPUT
TOUCH SENSOR FOR USER INPUT
Real-Time Adaptive Noise Cancellation System
POWER SUPPLY UNIT
MICRO CONTROLLER ESP-32
MICRO PHONE FOR NOISE INPUT
OLED DISPLAY
MICRO PHONE FOR USER INPUT

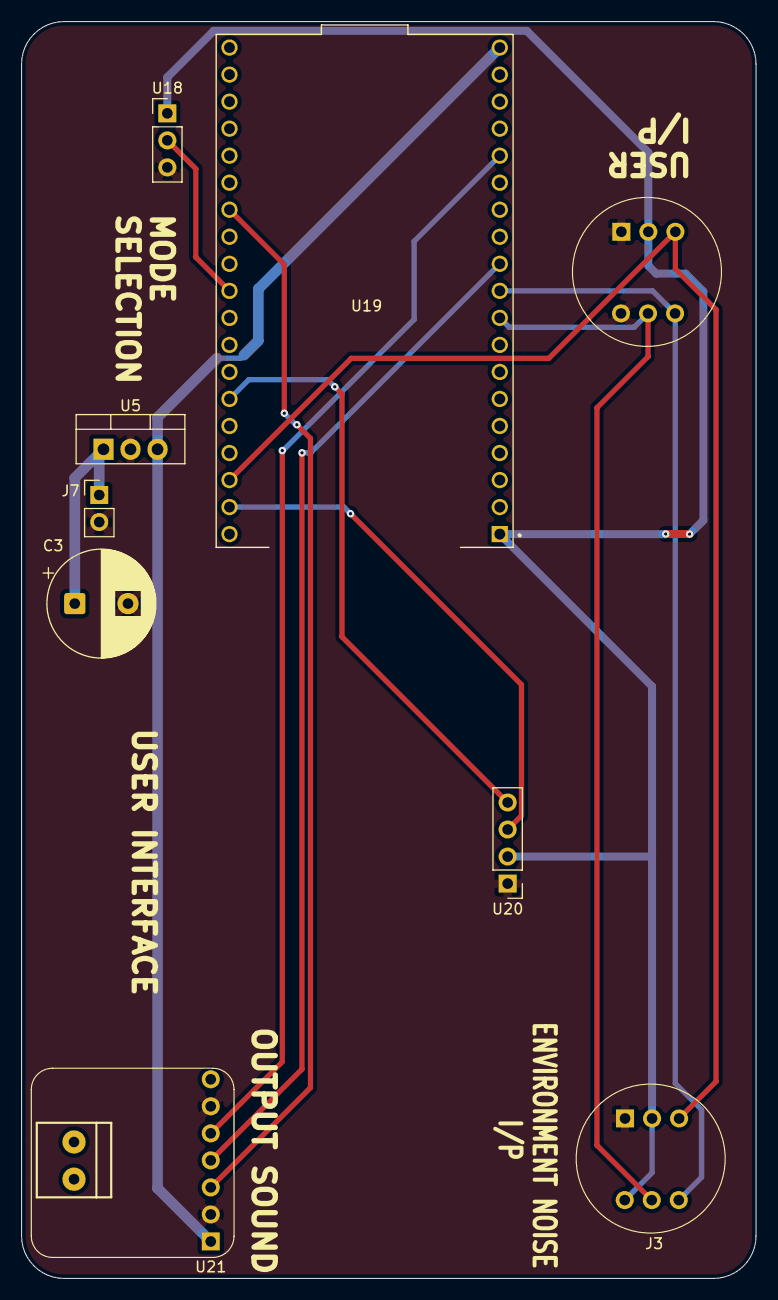
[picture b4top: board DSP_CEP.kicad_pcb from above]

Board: 2 copper layers, 69.0 x 118.1 mm, 9 parts (0 on the bottom side), 13 nets.

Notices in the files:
README.md:
License: MIT
